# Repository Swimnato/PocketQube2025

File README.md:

# PocketQube2025
Source code for the processing portion of the BYU spacecraft club's Pocket Qube Sat 2025

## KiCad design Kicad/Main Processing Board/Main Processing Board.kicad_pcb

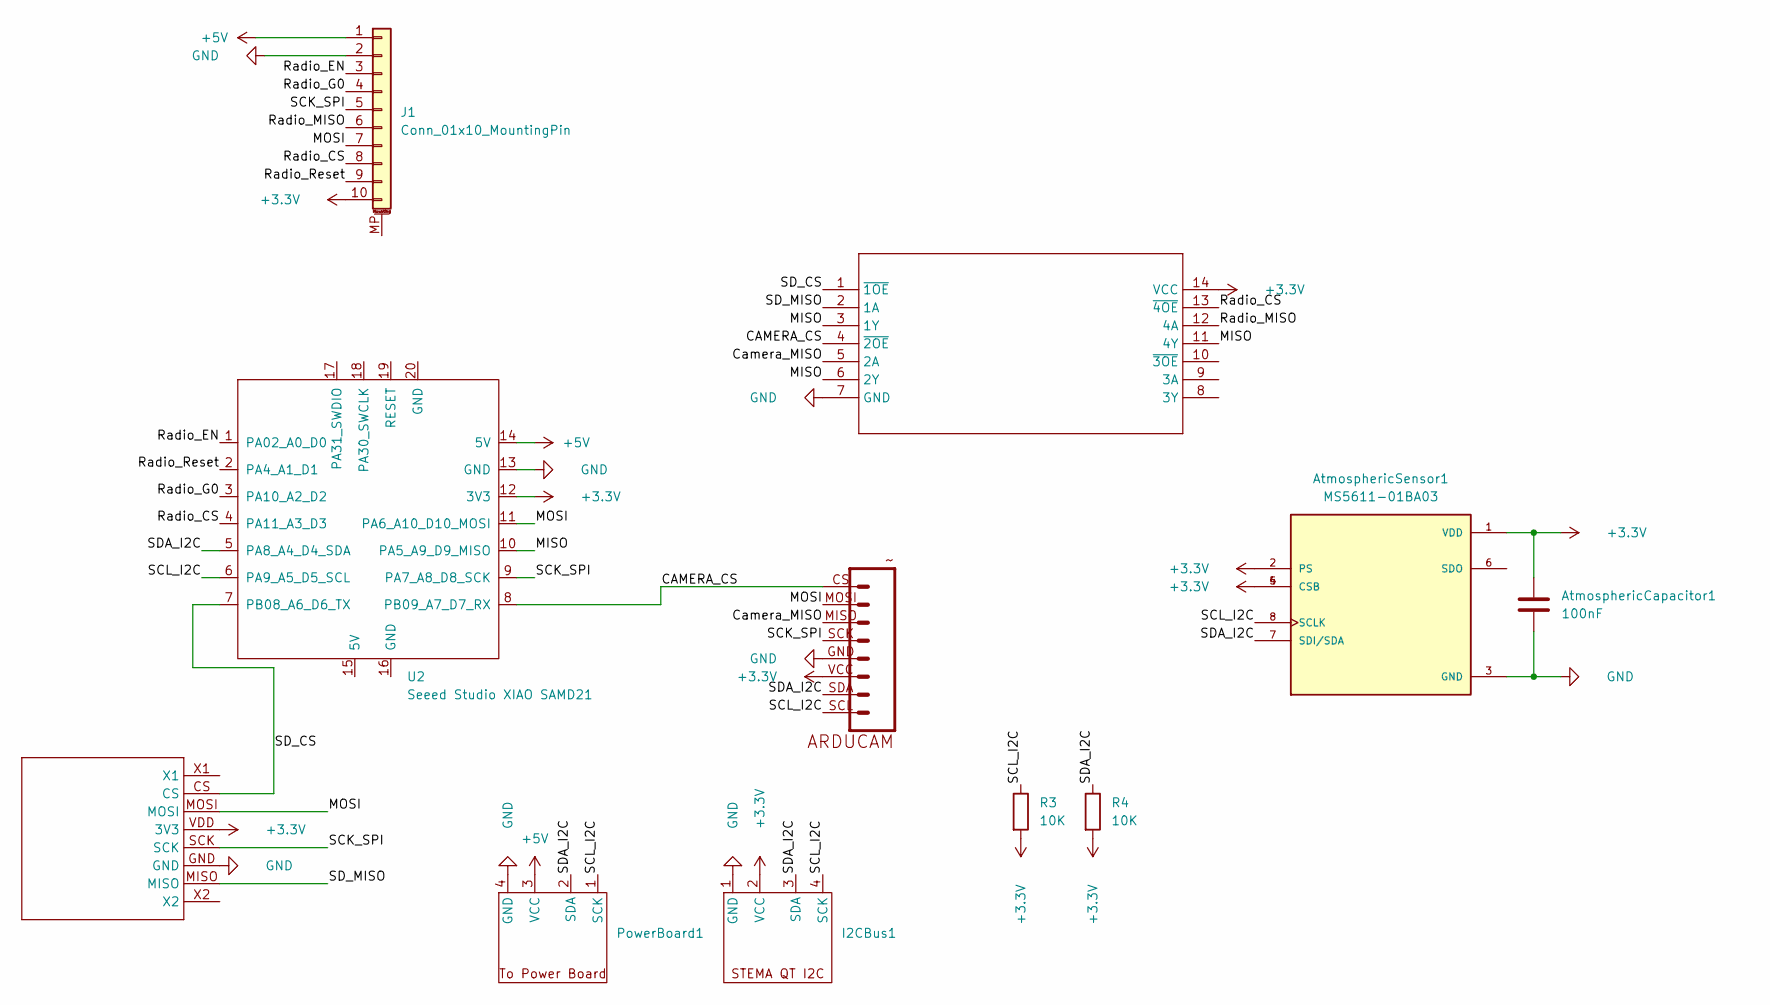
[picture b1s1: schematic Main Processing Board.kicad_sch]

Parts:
11111: SDREAD
12111: ARDUCAM_MINI
AtmosphericCapacitor1: 100nF
AtmosphericSensor1: MS5611-01BA03; SON125P500X300X100-8N; PARTREV 06/2017
I2CBus1: JST_SH_BM04B-SRSS-TB_1x04-1MP_P1.00mm_Vertical
J1: Conn_01x10_MountingPin; JST_SH_BM10B-SRSS-TB_1x10-1MP_P1.00mm_Vertical
PowerBoard1: Molex_PicoBlade_53047-0410_1x04_P1.25mm_Vertical
R3, R4: 10K
U1: NS14
U2: Seeed Studio XIAO SAMD21; XIAO-SAMD21-SMD

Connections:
+3.3V: 11111.VDD (3V3), 12111.VCC, AtmosphericCapacitor1.1, AtmosphericSensor1.1 (VDD), AtmosphericSensor1.2 (PS), AtmosphericSensor1.4 (CSB), AtmosphericSensor1.5 (CSB), I2CBus1.2 (VCC), J1.10, R3.2, R4.2, U1.14 (VCC), U2.12 (3V3)
+5V: J1.1, PowerBoard1.3 (VCC), U2.14 (5V)
/CAMERA_CS: 12111.CS, U1.4 (~2OE), U2.8 (PB09_A7_D7_RX)
/Camera_MISO: 12111.MISO, U1.5 (2A)
/MISO: U1.3 (1Y), U1.6 (2Y), U1.11 (4Y), U2.10 (PA5_A9_D9_MISO)
/MOSI: 11111.MOSI, 12111.MOSI, J1.7, U2.11 (PA6_A10_D10_MOSI)
/Radio_CS: J1.8, U1.13 (~4OE), U2.4 (PA11_A3_D3)
/Radio_EN: J1.3, U2.1 (PA02_A0_D0)
/Radio_G0: J1.4, U2.3 (PA10_A2_D2)
/Radio_MISO: J1.6, U1.12 (4A)
/Radio_Reset: J1.9, U2.2 (PA4_A1_D1)
/SCK_SPI: 11111.SCK, 12111.SCK, J1.5, U2.9 (PA7_A8_D8_SCK)
/SCL_I2C: 12111.SCL, AtmosphericSensor1.8 (SCLK), I2CBus1.4 (SCK), PowerBoard1.1 (SCK), R3.1, U2.6 (PA9_A5_D5_SCL)
/SDA_I2C: 12111.SDA, AtmosphericSensor1.7 (SDI/SDA), I2CBus1.3 (SDA), PowerBoard1.2 (SDA), R4.1, U2.5 (PA8_A4_D4_SDA)
/SD_CS: 11111.CS, U1.1 (~1OE), U2.7 (PB08_A6_D6_TX)
/SD_MISO: 11111.MISO, U1.2 (1A)
GND: 11111.GND, 12111.GND, AtmosphericCapacitor1.2, AtmosphericSensor1.3 (GND), I2CBus1.1 (GND), J1.2, PowerBoard1.4 (GND), U1.7 (GND), U2.13 (GND)

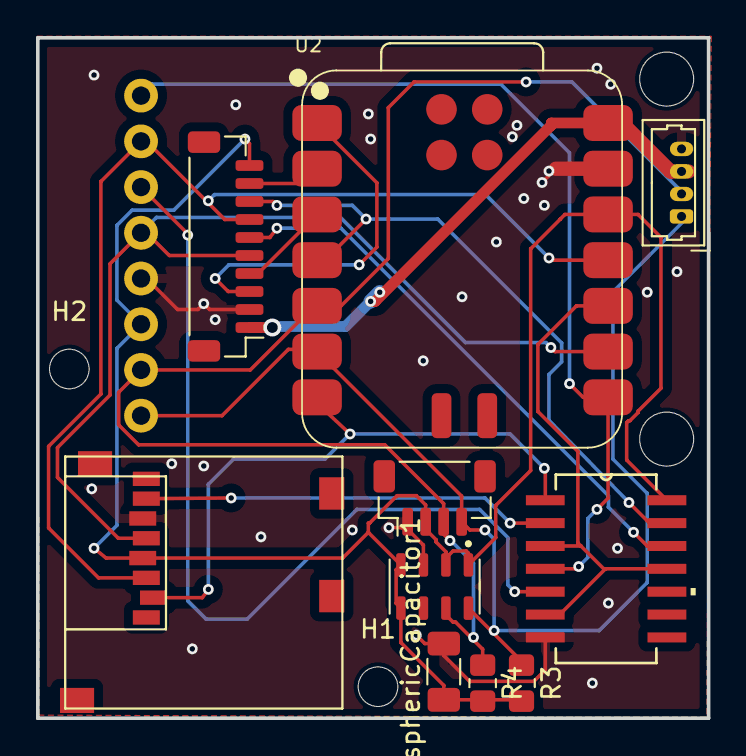
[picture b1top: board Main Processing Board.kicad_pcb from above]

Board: 2 copper layers, 37.3 x 37.8 mm, 13 parts (1 on the bottom side), 17 nets.

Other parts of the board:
H1, H2: MountingHole; MountingHole_2.2mm_M2

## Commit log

2024-11-13 Initial code
2024-11-13 make kicad project
    - Added libraries
    - Added test modules
2024-11-20 added old main
2024-11-20 renamed old main
2024-11-20 added old EAGLE files for the board. should have most things
2024-11-21 some added parts
2024-11-27 Wired SD card and Camera
    - Made new schematic for RA4M1
    - Made I2C and SPI labels
    - Started wiring
2025-02-17 fixed project io compiler
2025-02-19 added basis for main system
2025-02-19 updated line spacing
2025-02-20 added dataLogger structure
2025-02-20 more strictly enforced uart adherence
2025-02-20 added debug warning
2025-02-20 more work on kicad
2025-02-24 Added the sensors.h file. LSM and MMC functionality should be good
2025-02-26 updates to pcb and code
2025-02-26 added busIO lib
2025-02-26 added 3d models
2025-02-27 routed pcb
2025-02-27 not done with code, but need to grab kicad files
2025-02-27 added the ms.h file and fixed the code. Everything outputs as string or float
2025-03-05 updated pcb
    -added silkscreen
2025-03-05 added sensor lib
2025-03-05 Fixed cpp bugs
2025-03-05 closed kicad
2025-03-05 added power directory
2025-03-05 Uploaded Power Sensor Library
    Code for monitoring power, current, and voltage from INA_260 sensors.
    powerMonitor.h and example code called working_code.ino
2025-03-05 fixed sensor bug added power dependencies
2025-03-05 updated ms5611
2025-03-06 optimized and cleaned up some sensor code
2025-03-06 added power lib
2025-03-26 Added cpp file for radio
2025-03-26 started radio files
2025-03-26 a few small additions to init
2025-04-01 Fixed Compile issues
    To do: Find Radio Library
2025-04-02 added radio dependencies
2025-04-02 radio header file
2025-04-02 Added rx and sleep functionality to radio.cpp and updated radio.h
2025-04-02 Reorganized code to improve readability
2025-04-02 updated the code to work
    - we are only now experiencing software problems
2025-04-08 make radio a class and do some reorganizing
2025-04-08 started state machine refactor
2025-04-08 move transitions and actions
2025-04-08 added some comments
2025-04-08 more radio setup and configuration
2025-04-08 prep for radio transmit code
2025-05-07 pin changes
2025-06-18 radio stuff done
2025-06-18 fixed pins
2025-06-20 Finalized code for sensors and SD card
2025-06-20 Fixed Pin definitions
2025-06-21 code for groundstation
2025-06-21 hope this works
2025-06-21 font
2025-06-21 fix small bug
2025-06-21 added radio code
2025-06-21 better groundstations
2025-06-21 Made it so radio doesn't freeze the system if LoRa Fails
